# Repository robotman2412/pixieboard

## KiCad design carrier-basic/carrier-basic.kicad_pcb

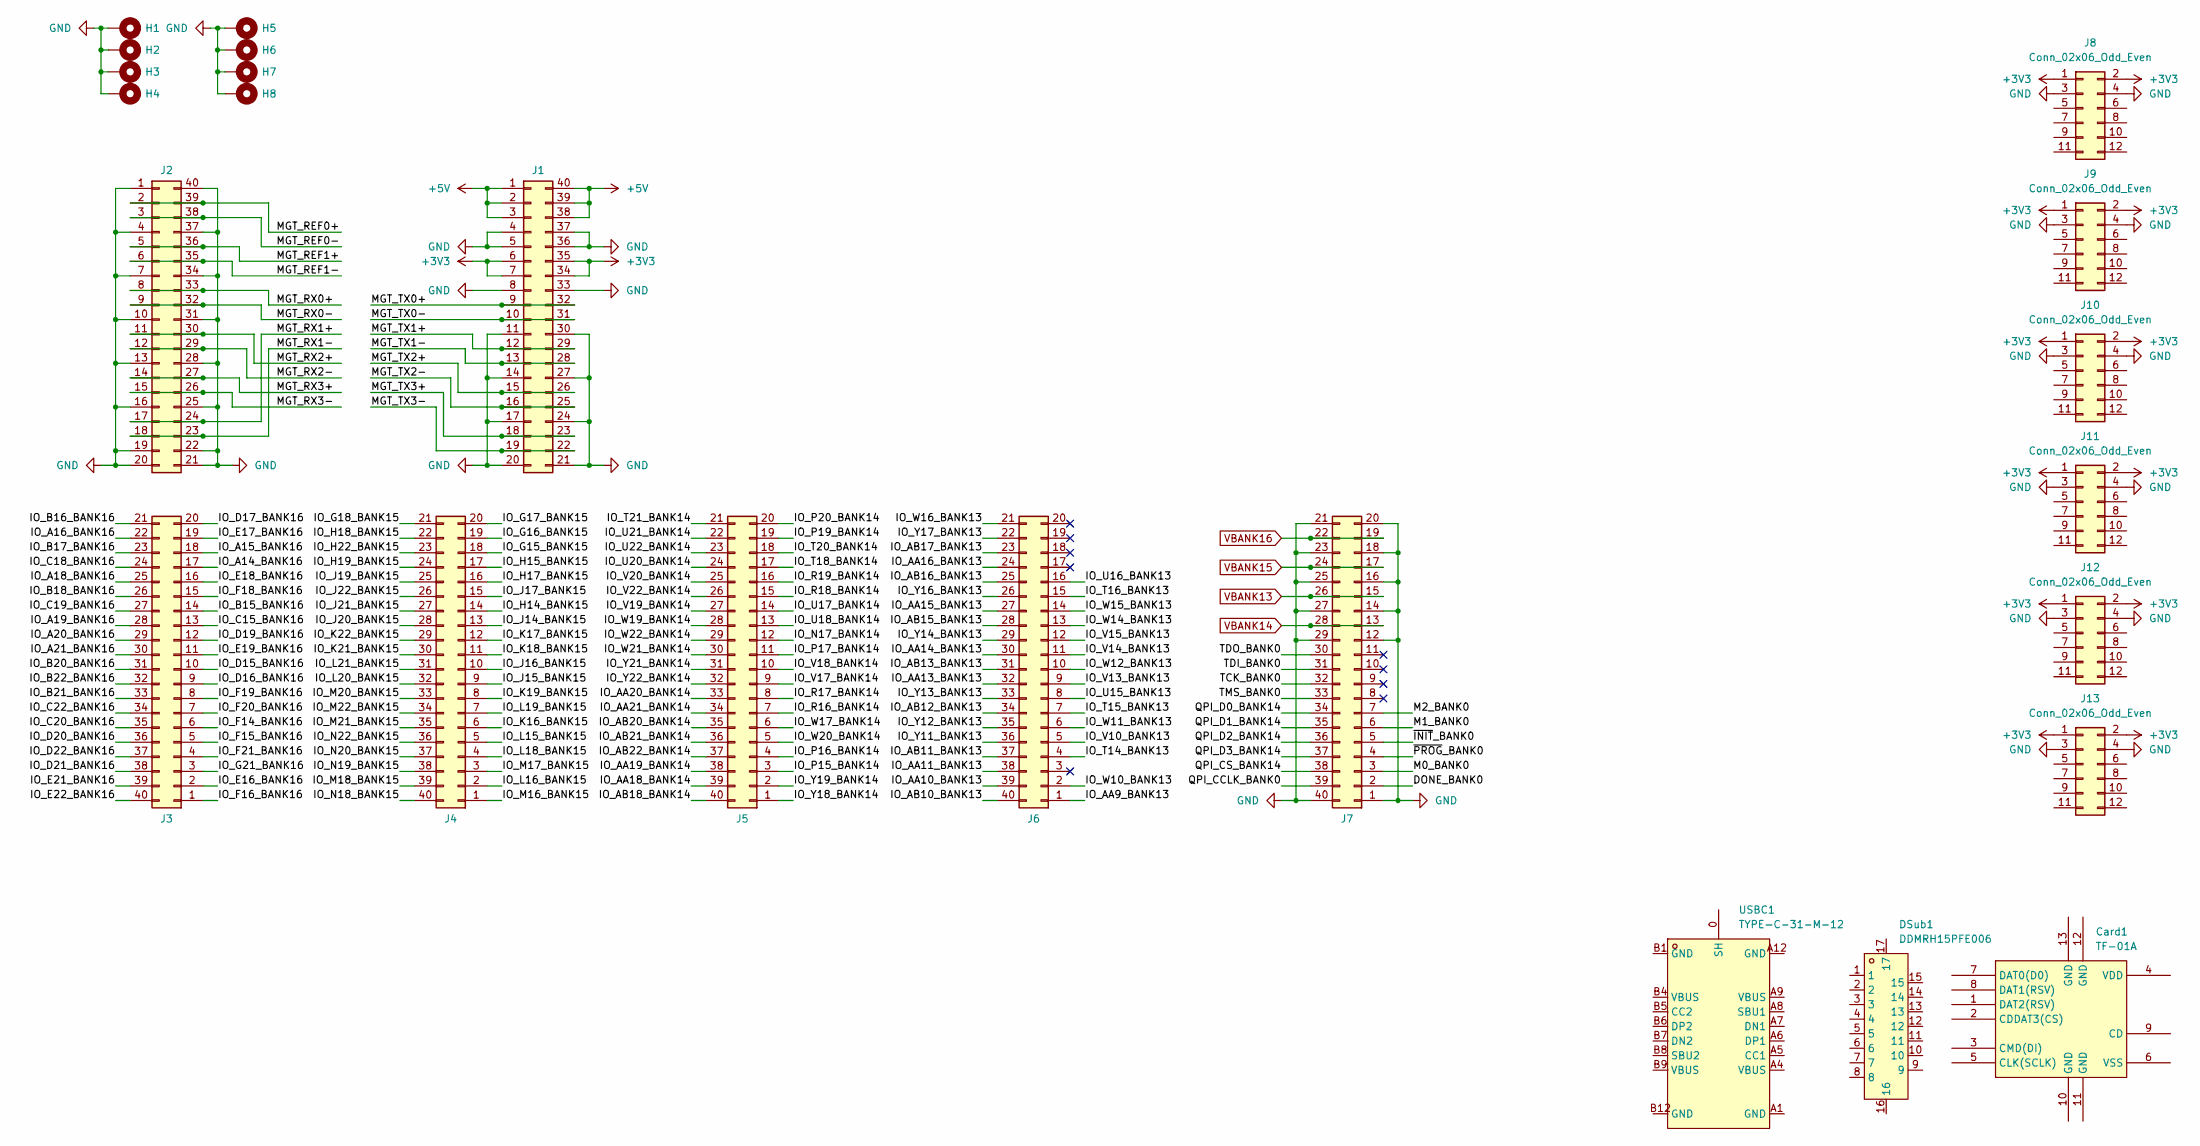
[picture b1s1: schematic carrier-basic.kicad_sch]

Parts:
Card1: TF-01A; TF-SMD_TF-01A; LCSC Part C91145
DSub1: DDMRH15PFE006; DSUB-TH_15P-P2.29-H-F_DDMRH15PFE006; LCSC Part C379814
H1, H2, H3, H4: MountingHole_Pad; MountingHole_2.2mm_M2_DIN965_Pad
H5, H6, H7, H8: MountingHole_Pad; MountingHole_4mm_Pad
J1, J2, J3, J4, J5, J6, J7: Conn_02x20_Counter_Clockwise; YXT-BB10-40S-02
J8, J9, J10, J11, J12, J13: Conn_02x06_Odd_Even; PinSocket_2x06_P2.54mm_Horizontal
USBC1: TYPE-C-31-M-12; USB-C_SMD-TYPE-C-31-M-12; LCSC Part C165948

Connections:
+3V3: J1.6, J1.7, J1.34, J1.35, J8.1, J8.2, J9.1, J9.2, J10.1, J10.2, J11.1, J11.2, J12.1, J12.2, J13.1, J13.2
+5V: J1.1, J1.2, J1.3, J1.38, J1.39, J1.40
/DONE_BANK0: J7.2
/IO_A14_BANK16: J3.17
/IO_A15_BANK16: J3.18
/IO_A16_BANK16: J3.22
/IO_A18_BANK16: J3.25
/IO_A19_BANK16: J3.28
/IO_A20_BANK16: J3.29
/IO_A21_BANK16: J3.30
/IO_AA9_BANK13: J6.1
/IO_AA10_BANK13: J6.39
/IO_AA11_BANK13: J6.38
/IO_AA13_BANK13: J6.32
/IO_AA14_BANK13: J6.30
/IO_AA15_BANK13: J6.27
/IO_AA16_BANK13: J6.24
/IO_AA18_BANK14: J5.39
/IO_AA19_BANK14: J5.38
/IO_AA20_BANK14: J5.33
/IO_AA21_BANK14: J5.34
/IO_AB10_BANK13: J6.40
/IO_AB11_BANK13: J6.37
/IO_AB12_BANK13: J6.34
/IO_AB13_BANK13: J6.31
/IO_AB15_BANK13: J6.28
/IO_AB16_BANK13: J6.25
/IO_AB17_BANK13: J6.23
/IO_AB18_BANK14: J5.40
/IO_AB20_BANK14: J5.35
/IO_AB21_BANK14: J5.36
/IO_AB22_BANK14: J5.37
/IO_B15_BANK16: J3.14
/IO_B16_BANK16: J3.21
/IO_B17_BANK16: J3.23
/IO_B18_BANK16: J3.26
/IO_B20_BANK16: J3.31
/IO_B21_BANK16: J3.33
/IO_B22_BANK16: J3.32
/IO_C15_BANK16: J3.13
/IO_C18_BANK16: J3.24
/IO_C19_BANK16: J3.27
/IO_C20_BANK16: J3.35
/IO_C22_BANK16: J3.34
/IO_D15_BANK16: J3.10
/IO_D16_BANK16: J3.9
/IO_D17_BANK16: J3.20
/IO_D19_BANK16: J3.12
/IO_D20_BANK16: J3.36
/IO_D21_BANK16: J3.38
/IO_D22_BANK16: J3.37
/IO_E16_BANK16: J3.2
/IO_E17_BANK16: J3.19
/IO_E18_BANK16: J3.16
/IO_E19_BANK16: J3.11
/IO_E21_BANK16: J3.39
/IO_E22_BANK16: J3.40
/IO_F14_BANK16: J3.6
/IO_F15_BANK16: J3.5
/IO_F16_BANK16: J3.1
/IO_F18_BANK16: J3.15
/IO_F19_BANK16: J3.8
/IO_F20_BANK16: J3.7
/IO_F21_BANK16: J3.4
/IO_G15_BANK15: J4.18
/IO_G16_BANK15: J4.19
/IO_G17_BANK15: J4.20
/IO_G18_BANK15: J4.21
/IO_G21_BANK16: J3.3
/IO_H14_BANK15: J4.14
/IO_H15_BANK15: J4.17
/IO_H17_BANK15: J4.16
/IO_H18_BANK15: J4.22
/IO_H19_BANK15: J4.24
/IO_H22_BANK15: J4.23
/IO_J14_BANK15: J4.13
/IO_J15_BANK15: J4.9
/IO_J16_BANK15: J4.10
/IO_J17_BANK15: J4.15
/IO_J19_BANK15: J4.25
/IO_J20_BANK15: J4.28
/IO_J21_BANK15: J4.27
/IO_J22_BANK15: J4.26
/IO_K16_BANK15: J4.6
/IO_K17_BANK15: J4.12
/IO_K18_BANK15: J4.11
/IO_K19_BANK15: J4.8
/IO_K21_BANK15: J4.30
/IO_K22_BANK15: J4.29
/IO_L15_BANK15: J4.5
/IO_L16_BANK15: J4.2
/IO_L18_BANK15: J4.4
/IO_L19_BANK15: J4.7
/IO_L20_BANK15: J4.32
/IO_L21_BANK15: J4.31
/IO_M16_BANK15: J4.1
/IO_M17_BANK15: J4.3
/IO_M18_BANK15: J4.39
/IO_M20_BANK15: J4.33
/IO_M21_BANK15: J4.35
/IO_M22_BANK15: J4.34
/IO_N17_BANK14: J5.12
/IO_N18_BANK15: J4.40
/IO_N19_BANK15: J4.38
/IO_N20_BANK15: J4.37
/IO_N22_BANK15: J4.36
/IO_P15_BANK14: J5.3
/IO_P16_BANK14: J5.4
/IO_P17_BANK14: J5.11
/IO_P19_BANK14: J5.19
/IO_P20_BANK14: J5.20
/IO_R16_BANK14: J5.7
/IO_R17_BANK14: J5.8
/IO_R18_BANK14: J5.15
/IO_R19_BANK14: J5.16
/IO_T14_BANK13: J6.4
/IO_T15_BANK13: J6.7
/IO_T16_BANK13: J6.15
/IO_T18_BANK14: J5.17
/IO_T20_BANK14: J5.18
/IO_T21_BANK14: J5.21
/IO_U15_BANK13: J6.8
/IO_U16_BANK13: J6.16
/IO_U17_BANK14: J5.14
/IO_U18_BANK14: J5.13
/IO_U20_BANK14: J5.24
/IO_U21_BANK14: J5.22
/IO_U22_BANK14: J5.23
/IO_V10_BANK13: J6.5
/IO_V13_BANK13: J6.9
/IO_V14_BANK13: J6.11
/IO_V15_BANK13: J6.12
/IO_V17_BANK14: J5.9
/IO_V18_BANK14: J5.10
/IO_V19_BANK14: J5.27
/IO_V20_BANK14: J5.25
/IO_V22_BANK14: J5.26
/IO_W10_BANK13: J6.2
/IO_W11_BANK13: J6.6
/IO_W12_BANK13: J6.10
/IO_W14_BANK13: J6.13
/IO_W15_BANK13: J6.14
/IO_W16_BANK13: J6.21
/IO_W17_BANK14: J5.6
/IO_W19_BANK14: J5.28
/IO_W20_BANK14: J5.5
/IO_W21_BANK14: J5.30
/IO_W22_BANK14: J5.29
/IO_Y11_BANK13: J6.36
/IO_Y12_BANK13: J6.35
/IO_Y13_BANK13: J6.33
/IO_Y14_BANK13: J6.29
/IO_Y16_BANK13: J6.26
/IO_Y17_BANK13: J6.22
/IO_Y18_BANK14: J5.1
/IO_Y19_BANK14: J5.2
/IO_Y21_BANK14: J5.31
/IO_Y22_BANK14: J5.32
/M0_BANK0: J7.3
/M1_BANK0: J7.6
/M2_BANK0: J7.7
/MGT_REF0+: J2.2, J2.39
/MGT_REF0-: J2.3, J2.38
/MGT_REF1+: J2.5, J2.36
/MGT_REF1-: J2.6, J2.35
/MGT_RX0+: J2.8, J2.33
/MGT_RX0-: J2.9, J2.32
/MGT_RX1+: J2.17, J2.24
/MGT_RX1-: J2.18, J2.23
/MGT_RX2+: J2.11, J2.30
/MGT_RX2-: J2.12, J2.29
/MGT_RX3+: J2.14, J2.27
/MGT_RX3-: J2.15, J2.26
/MGT_TX0+: J1.9, J1.32
/MGT_TX0-: J1.10, J1.31
/MGT_TX1+: J1.12, J1.29
/MGT_TX1-: J1.13, J1.28
/MGT_TX2+: J1.15, J1.26
/MGT_TX2-: J1.16, J1.25
/MGT_TX3+: J1.18, J1.23
/MGT_TX3-: J1.19, J1.22
/QPI_CCLK_BANK0: J7.39
/QPI_CS_BANK14: J7.38
/QPI_D0_BANK14: J7.34
/QPI_D1_BANK14: J7.35
/QPI_D2_BANK14: J7.36
/QPI_D3_BANK14: J7.37
/TCK_BANK0: J7.32
/TDI_BANK0: J7.31
/TDO_BANK0: J7.30
/TMS_BANK0: J7.33
/~INIT_BANK0: J7.5
/~PROG_BANK0: J7.4
GND: H1.1, H2.1, H3.1, H4.1, H5.1, H6.1, H7.1, H8.1, J1.4, J1.5, J1.8, J1.11, J1.14, J1.17, J1.20, J1.21, J1.24, J1.27, J1.30, J1.33, J1.36, J1.37, J2.1, J2.4, J2.7, J2.10, J2.13, J2.16, J2.19, J2.20, J2.21, J2.22, J2.25, J2.28, J2.31, J2.34, J2.37, J2.40, J7.1, J7.12, J7.14, J7.16, J7.18, J7.20, J7.21, J7.23, J7.25, J7.27, J7.29, J7.40, J8.3, J8.4, J9.3, J9.4, J10.3, J10.4, J11.3, J11.4, J12.3, J12.4, J13.3, J13.4
VBANK13: J7.15, J7.26
VBANK14: J7.13, J7.28
VBANK15: J7.17, J7.24
VBANK16: J7.19, J7.22

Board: 4 copper layers, 24 parts (0 on the bottom side), 27 nets, no tracks yet.

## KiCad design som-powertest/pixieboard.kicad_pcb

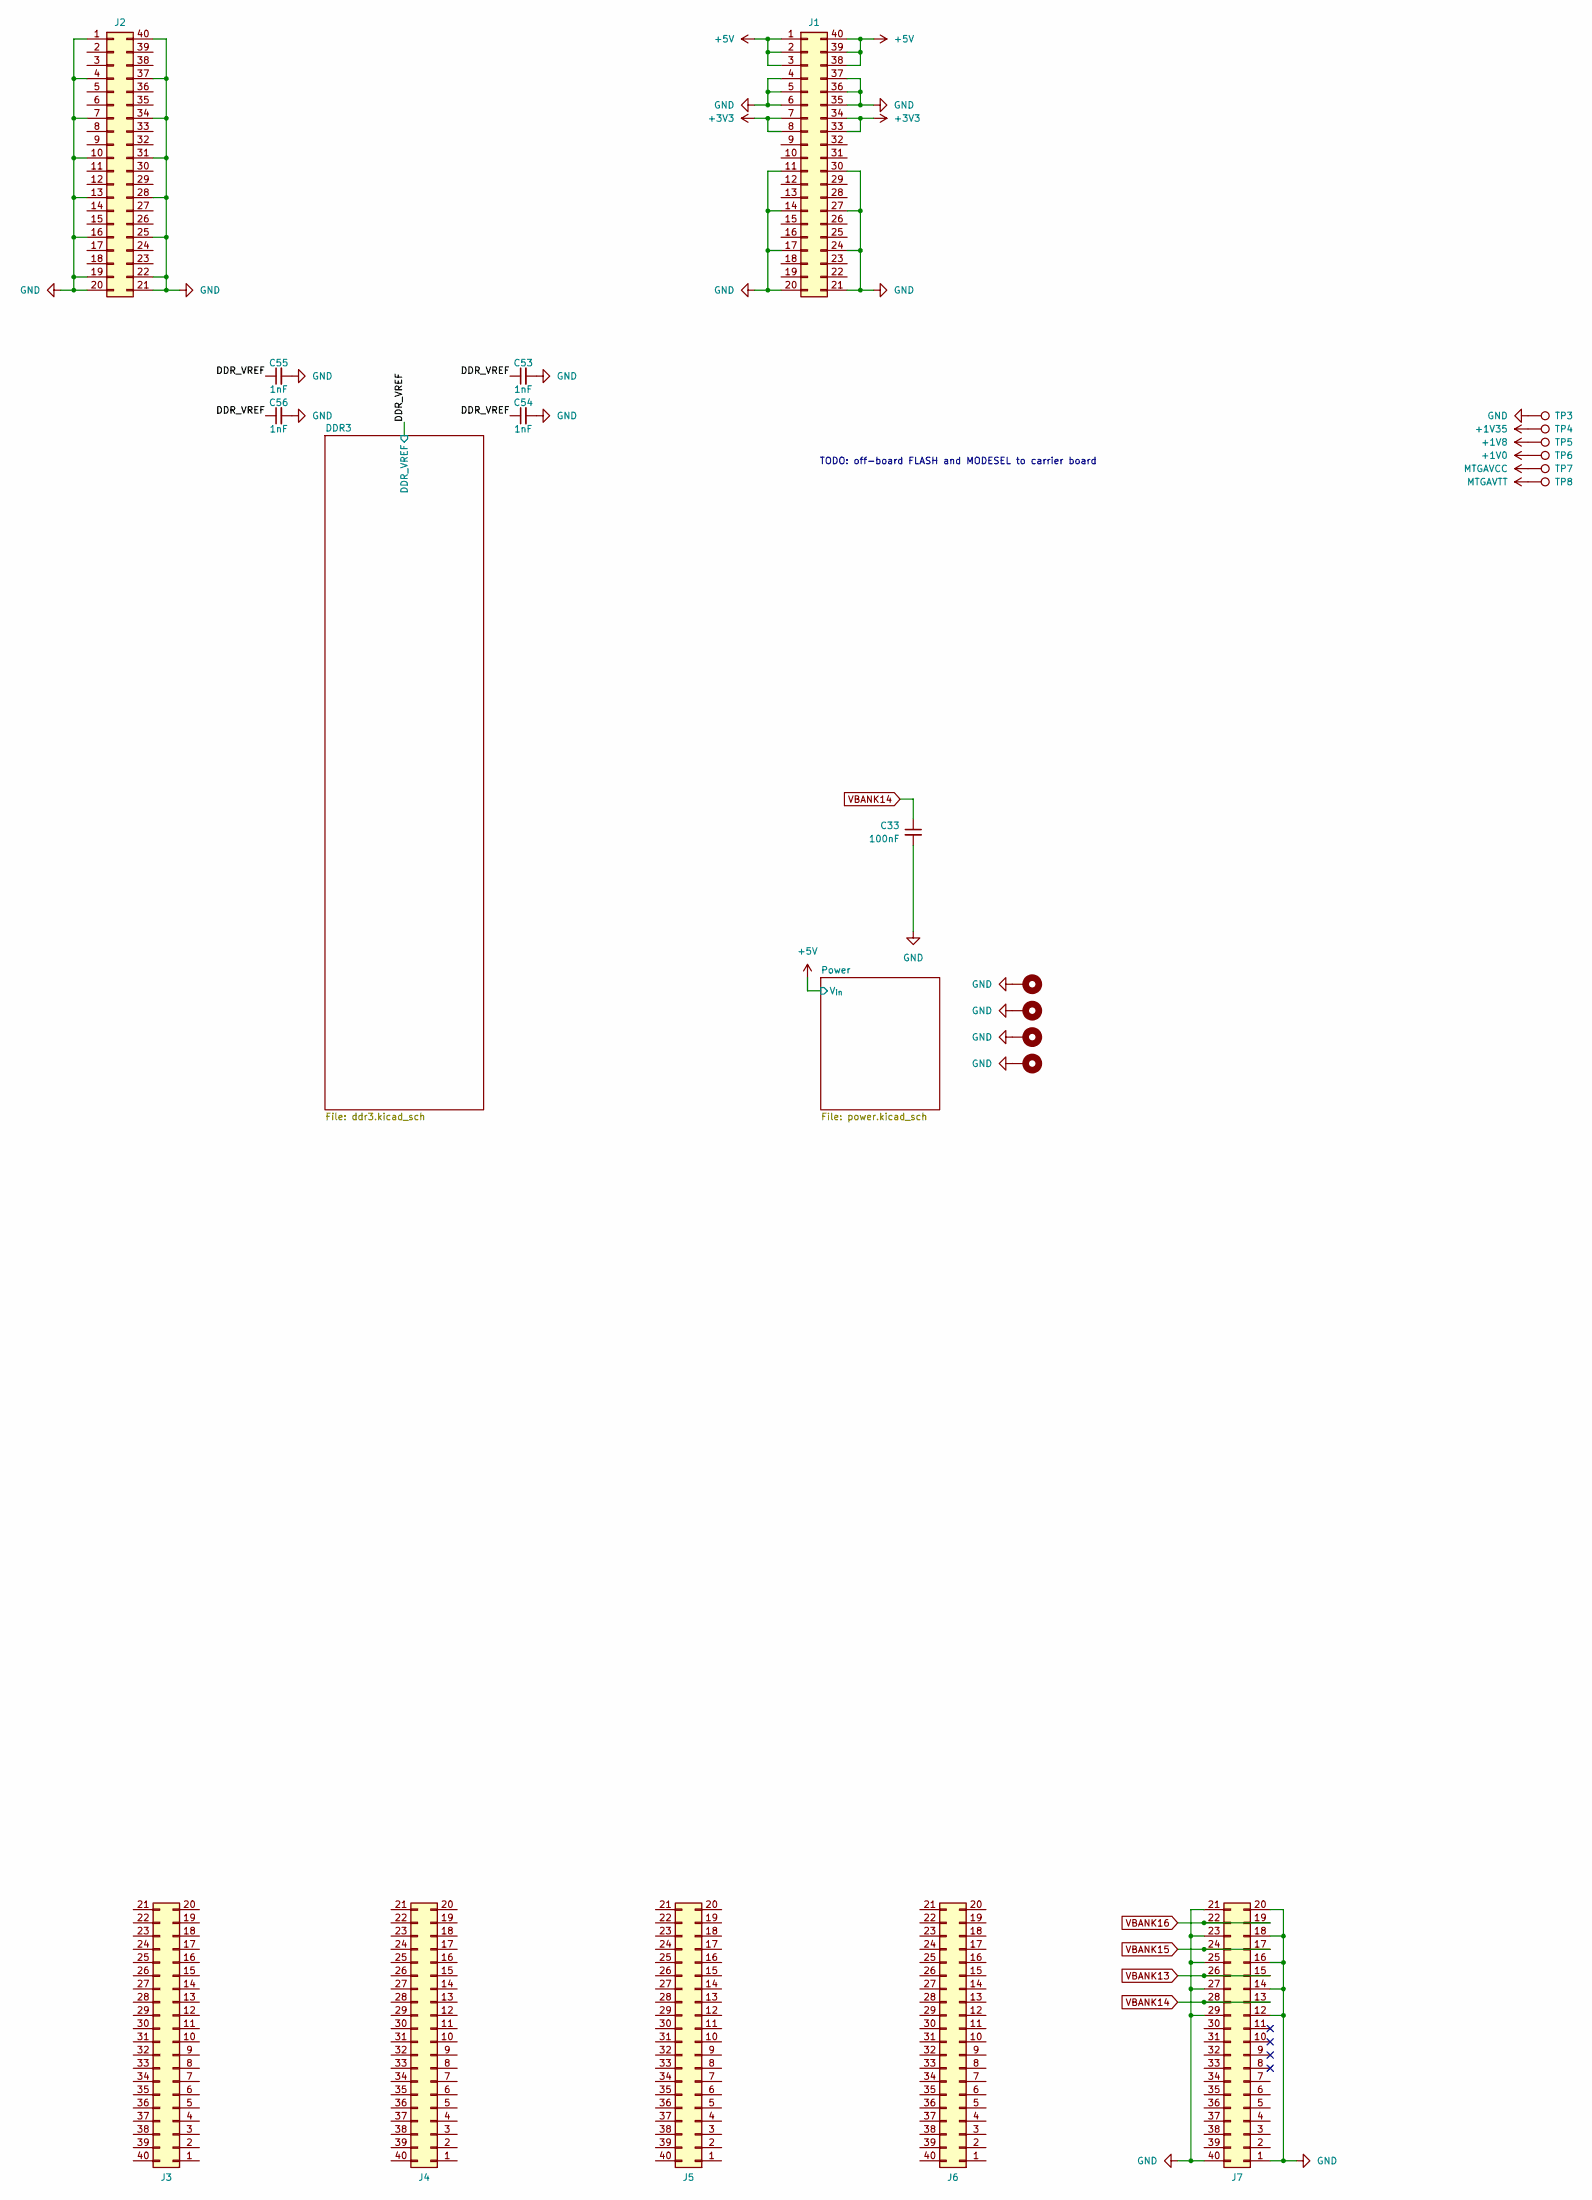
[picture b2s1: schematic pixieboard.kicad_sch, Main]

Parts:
C33: 100nF; C_0402_1005Metric
C53, C54, C55, C56: 1nF; C_0402_1005Metric
H1, H2, H3, H4: MountingHole_Pad; MountingHole_2.2mm_M2_DIN965_Pad
J1, J2, J3, J4, J5, J6, J7: Conn_02x20_Counter_Clockwise; YXT-BB10-40P-02
TP3, TP4, TP5, TP6, TP7, TP8: TestPoint; TestPoint_Pad_D1.0mm

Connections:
+1V0: TP6.1; also elsewhere on the board
+1V8: TP5.1; also elsewhere on the board
+1V35: TP4.1; also elsewhere on the board
+3V3: J1.7, J1.8, J1.33, J1.34; also elsewhere on the board
+5V: J1.1, J1.2, J1.3, J1.38, J1.39, J1.40; also elsewhere on the board
/DDR_VREF: C53.1, C54.1, C55.1, C56.1; also elsewhere on the board
GND: C33.2, C53.2, C54.2, C55.2, C56.2, H1.1, H2.1, H3.1, H4.1, J1.4, J1.5, J1.6, J1.11, J1.14, J1.17, J1.20, J1.21, J1.24, J1.27, J1.30, J1.35, J1.36, J1.37, J2.1, J2.4, J2.7, J2.10, J2.13, J2.16, J2.19, J2.20, J2.21, J2.22, J2.25, J2.28, J2.31, J2.34, J2.37, J2.40, J7.1, J7.12, J7.14, J7.16, J7.18, J7.20, J7.21, J7.23, J7.25, J7.27, J7.29, J7.40, TP3.1; also elsewhere on the board
MTGAVCC: TP7.1; also elsewhere on the board
MTGAVTT: TP8.1; also elsewhere on the board
VBANK13: J7.15, J7.26; also elsewhere on the board
VBANK14: C33.1, J7.13, J7.28; also elsewhere on the board
VBANK15: J7.17, J7.24; also elsewhere on the board
VBANK16: J7.19, J7.22; also elsewhere on the board

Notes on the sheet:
TODO: off-board FLASH and MODESEL to carrier board

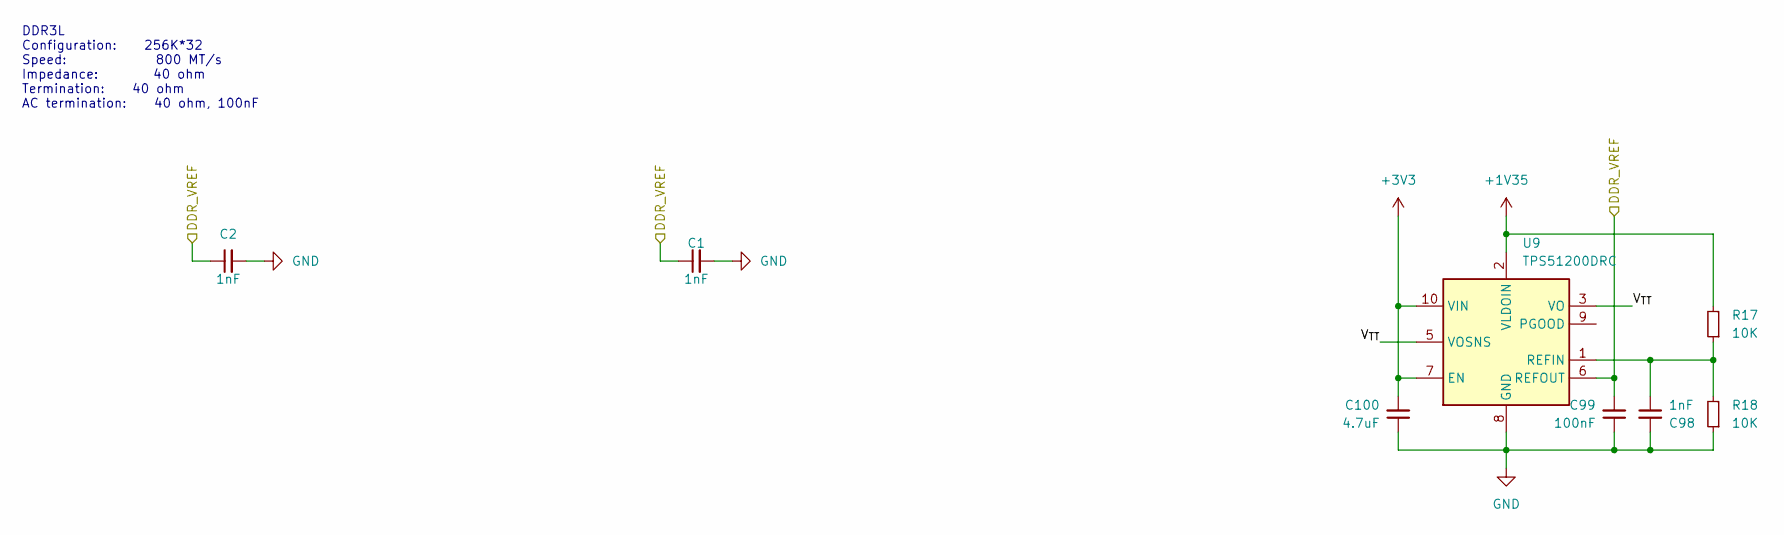
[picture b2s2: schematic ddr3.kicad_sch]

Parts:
C1, C2, C98: 1nF; C_0402_1005Metric
C99: 100nF; C_0402_1005Metric
C100: 4.7uF; C_0402_1005Metric
R17, R18: 10K; R_0402_1005Metric
U9: TPS51200DRC; VSON-10-1EP_3x3mm_P0.5mm_EP1.65x2.4mm; LCSC part number C34771

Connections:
+1V35: R17.2, U9.2 (VLDOIN); also elsewhere on the board
+3V3: C100.2, U9.7 (EN), U9.10 (VIN); also elsewhere on the board
/DDR3/V_{TT}: U9.3 (VO), U9.5 (VOSNS)
/DDR_VREF: C1.1, C2.1, C99.2, U9.6 (REFOUT); also elsewhere on the board
GND: C1.2, C2.2, C98.2, C99.1, C100.1, R18.1, U9.4 (GND), U9.8 (GND), U9.11 (GND); also elsewhere on the board
unnamed: C98.1, R17.1, R18.2, U9.1 (REFIN)

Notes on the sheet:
DDR3L Configuration: 256K*32 Speed: 800 MT/s Impedance: 40 ohm Termination: 40 ohm AC termination: 40 ohm, 100nF

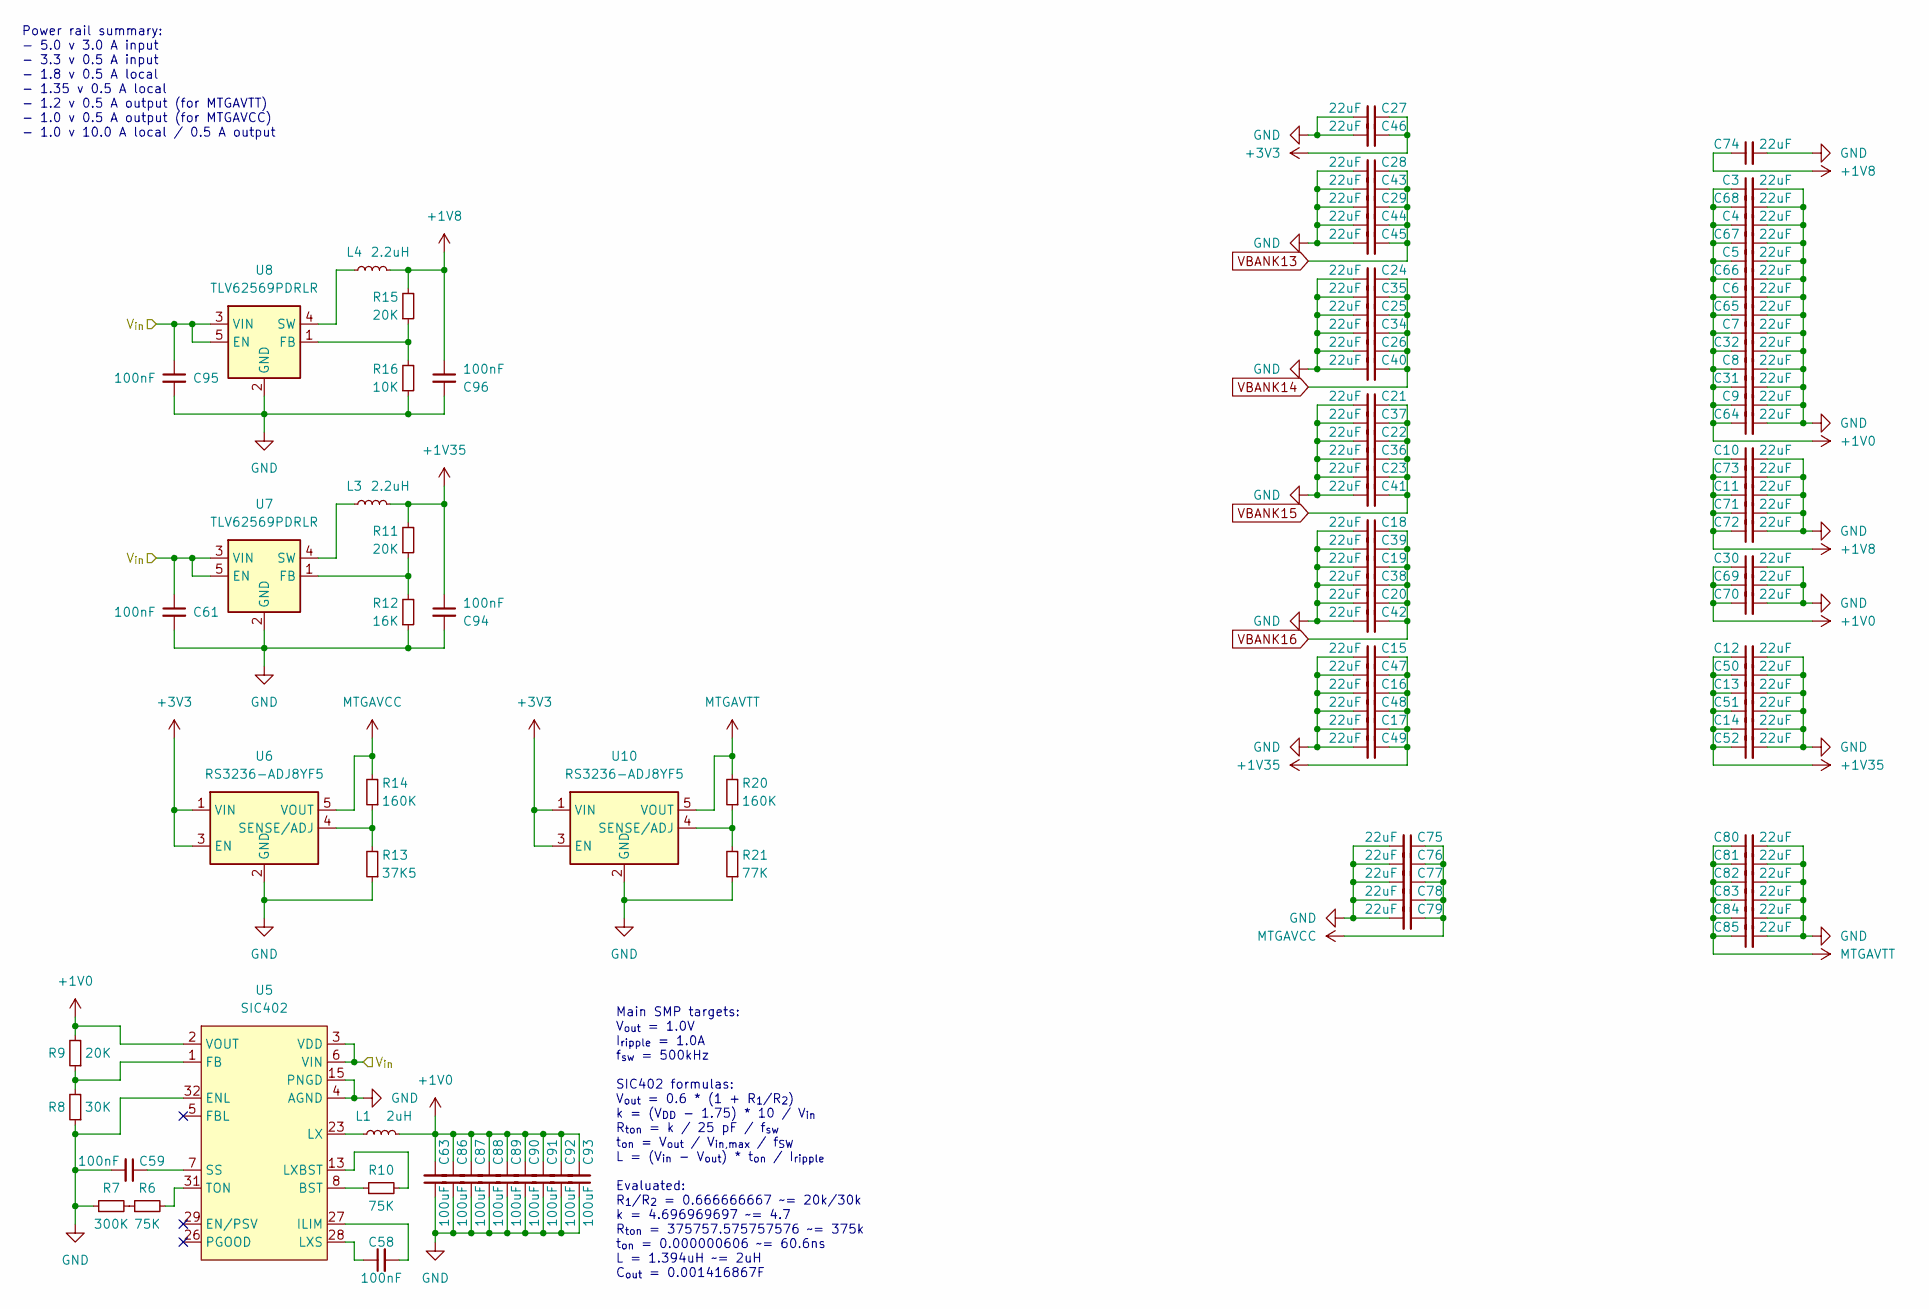
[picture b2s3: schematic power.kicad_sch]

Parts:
C3, C4, C5, C6, C7, C8, C9, C10, C11, C12, C13, C14, C15, C16, C17, C18, C19, C20, C21, C22, C23, C24, C25, C26, C27, C28, C29, C30, C31, C32, C34, C35, C36, C37, C38, C39, C40, C41, C42, C43, C44, C45, C46, C47, C48, C49, C50, C51, C52, C64, C65, C66, C67, C68, C69, C70, C71, C72, C73, C74, C75, C76, C77, C78, C79, C80, C81, C82, C83, C84, C85: 22uF; C_0402_1005Metric
C58, C59, C61, C94, C95, C96: 100nF; C_0402_1005Metric
C63, C86, C87, C88, C89, C90, C91, C92, C93: 100uF; C_1206_3216Metric
L1: 2uH; L_7.3x7.3_H3.5
L3, L4: 2.2uH; L_0603_1608Metric
R6, R10: 75K; R_0402_1005Metric_Pad0.72x0.64mm_HandSolder
R7: 300K; R_0402_1005Metric_Pad0.72x0.64mm_HandSolder
R8: 30K; R_0402_1005Metric_Pad0.72x0.64mm_HandSolder
R9, R11, R15: 20K; R_0402_1005Metric_Pad0.72x0.64mm_HandSolder
R12: 16K; R_0402_1005Metric_Pad0.72x0.64mm_HandSolder
R13: 37K5; R_0402_1005Metric_Pad0.72x0.64mm_HandSolder
R14, R20: 160K; R_0402_1005Metric_Pad0.72x0.64mm_HandSolder
R16: 10K; R_0402_1005Metric_Pad0.72x0.64mm_HandSolder
R21: 77K; R_0402_1005Metric_Pad0.72x0.64mm_HandSolder
U5: SIC402; LCSC part number C511100
U6, U10: RS3236-ADJ8YF5; TSOT-23-5; LCSC part number C379351
U7, U8: TLV62569PDRLR; SOT-563

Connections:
+1V0: C3.1, C4.1, C5.1, C6.1, C7.1, C8.1, C9.1, C30.1, C31.1, C32.1, C63.2, C64.1, C65.1, C66.1, C67.1, C68.1, C69.1, C70.1, C86.2, C87.2, C88.2, C89.2, C90.2, C91.2, C92.2, C93.2, L1.2, R9.2, U5.2 (VOUT); also elsewhere on the board
+1V8: C10.1, C11.1, C71.1, C72.1, C73.1, C74.1, C96.1, L4.2, R15.2; also elsewhere on the board
+1V35: C12.1, C13.1, C14.1, C15.1, C16.1, C17.1, C47.1, C48.1, C49.1, C50.1, C51.1, C52.1, C94.1, L3.2, R11.2; also elsewhere on the board
+3V3: C27.1, C46.1, U6.1 (VIN), U6.3 (EN), U10.1 (VIN), U10.3 (EN); also elsewhere on the board
+5V: C61.1, C95.1, U5.3 (VDD), U5.6 (VIN), U5.9 (VIN), U5.10 (VIN), U5.11 (VIN), U5.34 (VIN), U7.3 (VIN), U7.5 (EN), U8.3 (VIN), U8.5 (EN); also elsewhere on the board
GND: C3.2, C4.2, C5.2, C6.2, C7.2, C8.2, C9.2, C10.2, C11.2, C12.2, C13.2, C14.2, C15.2, C16.2, C17.2, C18.2, C19.2, C20.2, C21.2, C22.2, C23.2, C24.2, C25.2, C26.2, C27.2, C28.2, C29.2, C30.2, C31.2, C32.2, C34.2, C35.2, C36.2, C37.2, C38.2, C39.2, C40.2, C41.2, C42.2, C43.2, C44.2, C45.2, C46.2, C47.2, C48.2, C49.2, C50.2, C51.2, C52.2, C59.2, C61.2, C63.1, C64.2, C65.2, C66.2, C67.2, C68.2, C69.2, C70.2, C71.2, C72.2, C73.2, C74.2, C75.2, C76.2, C77.2, C78.2, C79.2, C80.2, C81.2, C82.2, C83.2, C84.2, C85.2, C86.1, C87.1, C88.1, C89.1, C90.1, C91.1, C92.1, C93.1, C94.2, C95.2, C96.2, R7.1, R8.1, R12.1, R13.1, R16.1, R21.1, U5.4 (AGND), U5.15 (PNGD), U5.16 (PNGD), U5.17 (PNGD), U5.18 (PNGD), U5.19 (PNGD), U5.20 (PNGD), U5.21 (PNGD), U5.22 (PNGD), U5.30 (AGND), U5.32 (ENL), U5.33 (AGND), U6.2 (GND), U7.2 (GND), U8.2 (GND), U10.2 (GND); also elsewhere on the board
MTGAVCC: C75.1, C76.1, C77.1, C78.1, C79.1, R14.2, U6.5 (VOUT); also elsewhere on the board
MTGAVTT: C80.1, C81.1, C82.1, C83.1, C84.1, C85.1, R20.2, U10.5 (VOUT); also elsewhere on the board
unnamed: L1.1, U5.23 (LX), U5.24 (LX), U5.25 (LX), U5.35 (LX)
unnamed: R6.1, R7.2
unnamed: R10.1, U5.8 (BST)
unnamed: R8.2, R9.1, U5.1 (FB)
unnamed: C58.2, U5.27 (ILIM)
unnamed: R10.2, U5.13 (LXBST)
unnamed: C58.1, U5.28 (LXS)
unnamed: C59.1, U5.7 (SS)
unnamed: R6.2, U5.31 (TON)
unnamed: R13.2, R14.1, U6.4 (SENSE/ADJ)
unnamed: R11.1, R12.2, U7.1 (FB)
unnamed: L3.1, U7.4 (SW)
unnamed: R15.1, R16.2, U8.1 (FB)
unnamed: L4.1, U8.4 (SW)
unnamed: R20.1, R21.2, U10.4 (SENSE/ADJ)
VBANK13: C28.1, C29.1, C43.1, C44.1, C45.1; also elsewhere on the board
VBANK14: C24.1, C25.1, C26.1, C34.1, C35.1, C40.1; also elsewhere on the board
VBANK15: C21.1, C22.1, C23.1, C36.1, C37.1, C41.1; also elsewhere on the board
VBANK16: C18.1, C19.1, C20.1, C38.1, C39.1, C42.1; also elsewhere on the board

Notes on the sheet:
Main SMP targets: V_{out} = 1.0V I_{ripple} = 1.0A f_{sw} = 500kHz SIC402 formulas: V_{out} = 0.6 * (1 + R_{1}/R_{2}) k = (V_{DD} - 1.75) * 10 / V_{in} R_{ton} = k / 25 pF / f_{sw} t_{on} = V_{out} / V_{in,max} / f_{SW} L = (V_{in} - V_{out}) * t_{on} / I_{ripple} Evaluated: R_{1}/R_{2} = 0.6666666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
Power rail summary: - 5.0 v 3.0 A input - 3.3 v 0.5 A input - 1.8 v 0.5 A local - 1.35 v 0.5 A local - 1.2 v 0.5 A output (for MTGAVTT) - 1.0 v 0.5 A output (for MTGAVCC) - 1.0 v 10.0 A local / 0.5 A output

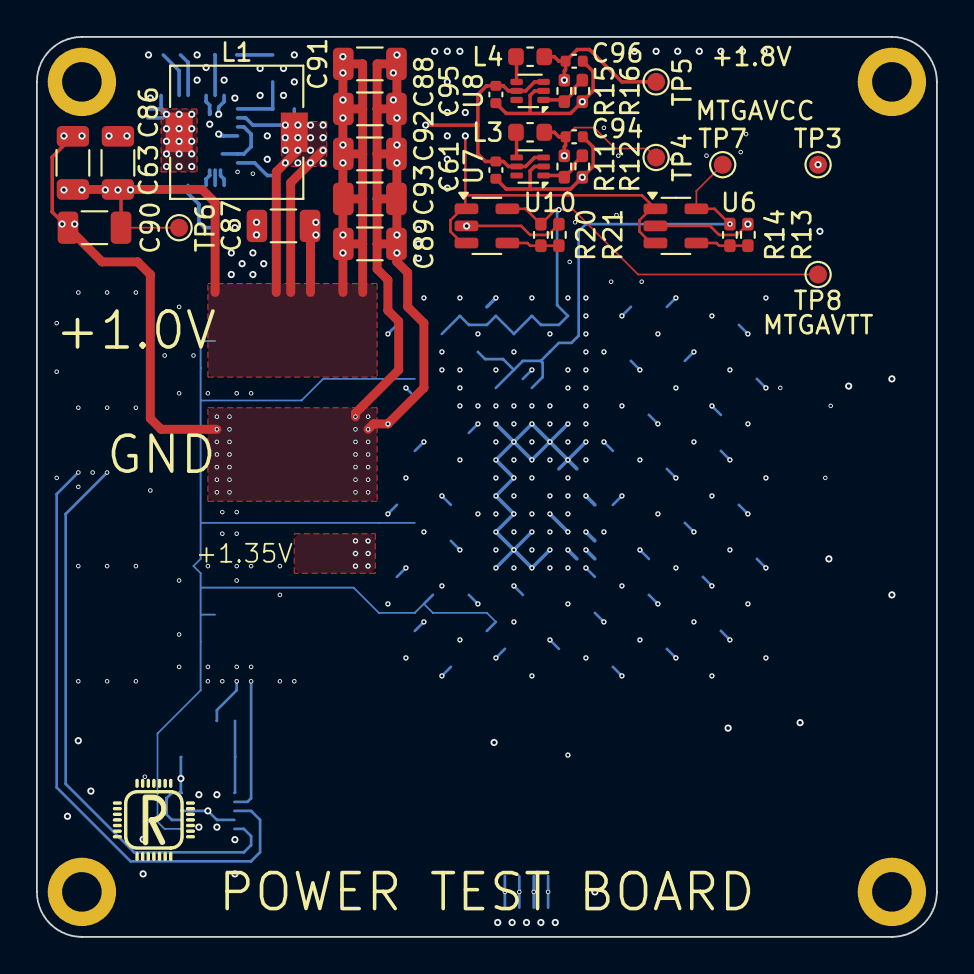
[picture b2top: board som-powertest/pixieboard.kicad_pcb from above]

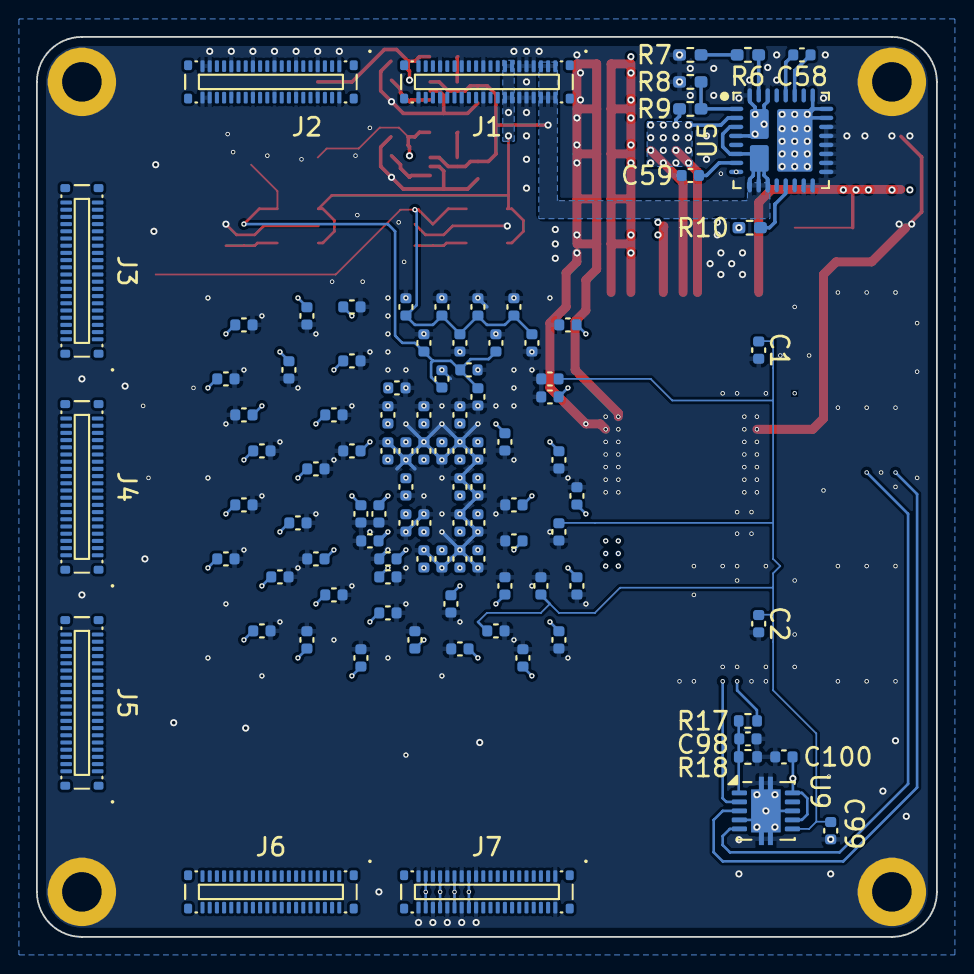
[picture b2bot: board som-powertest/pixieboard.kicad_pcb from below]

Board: 4 copper layers, 50.0 x 50.0 mm, 137 parts (99 on the bottom side), 30 nets.
